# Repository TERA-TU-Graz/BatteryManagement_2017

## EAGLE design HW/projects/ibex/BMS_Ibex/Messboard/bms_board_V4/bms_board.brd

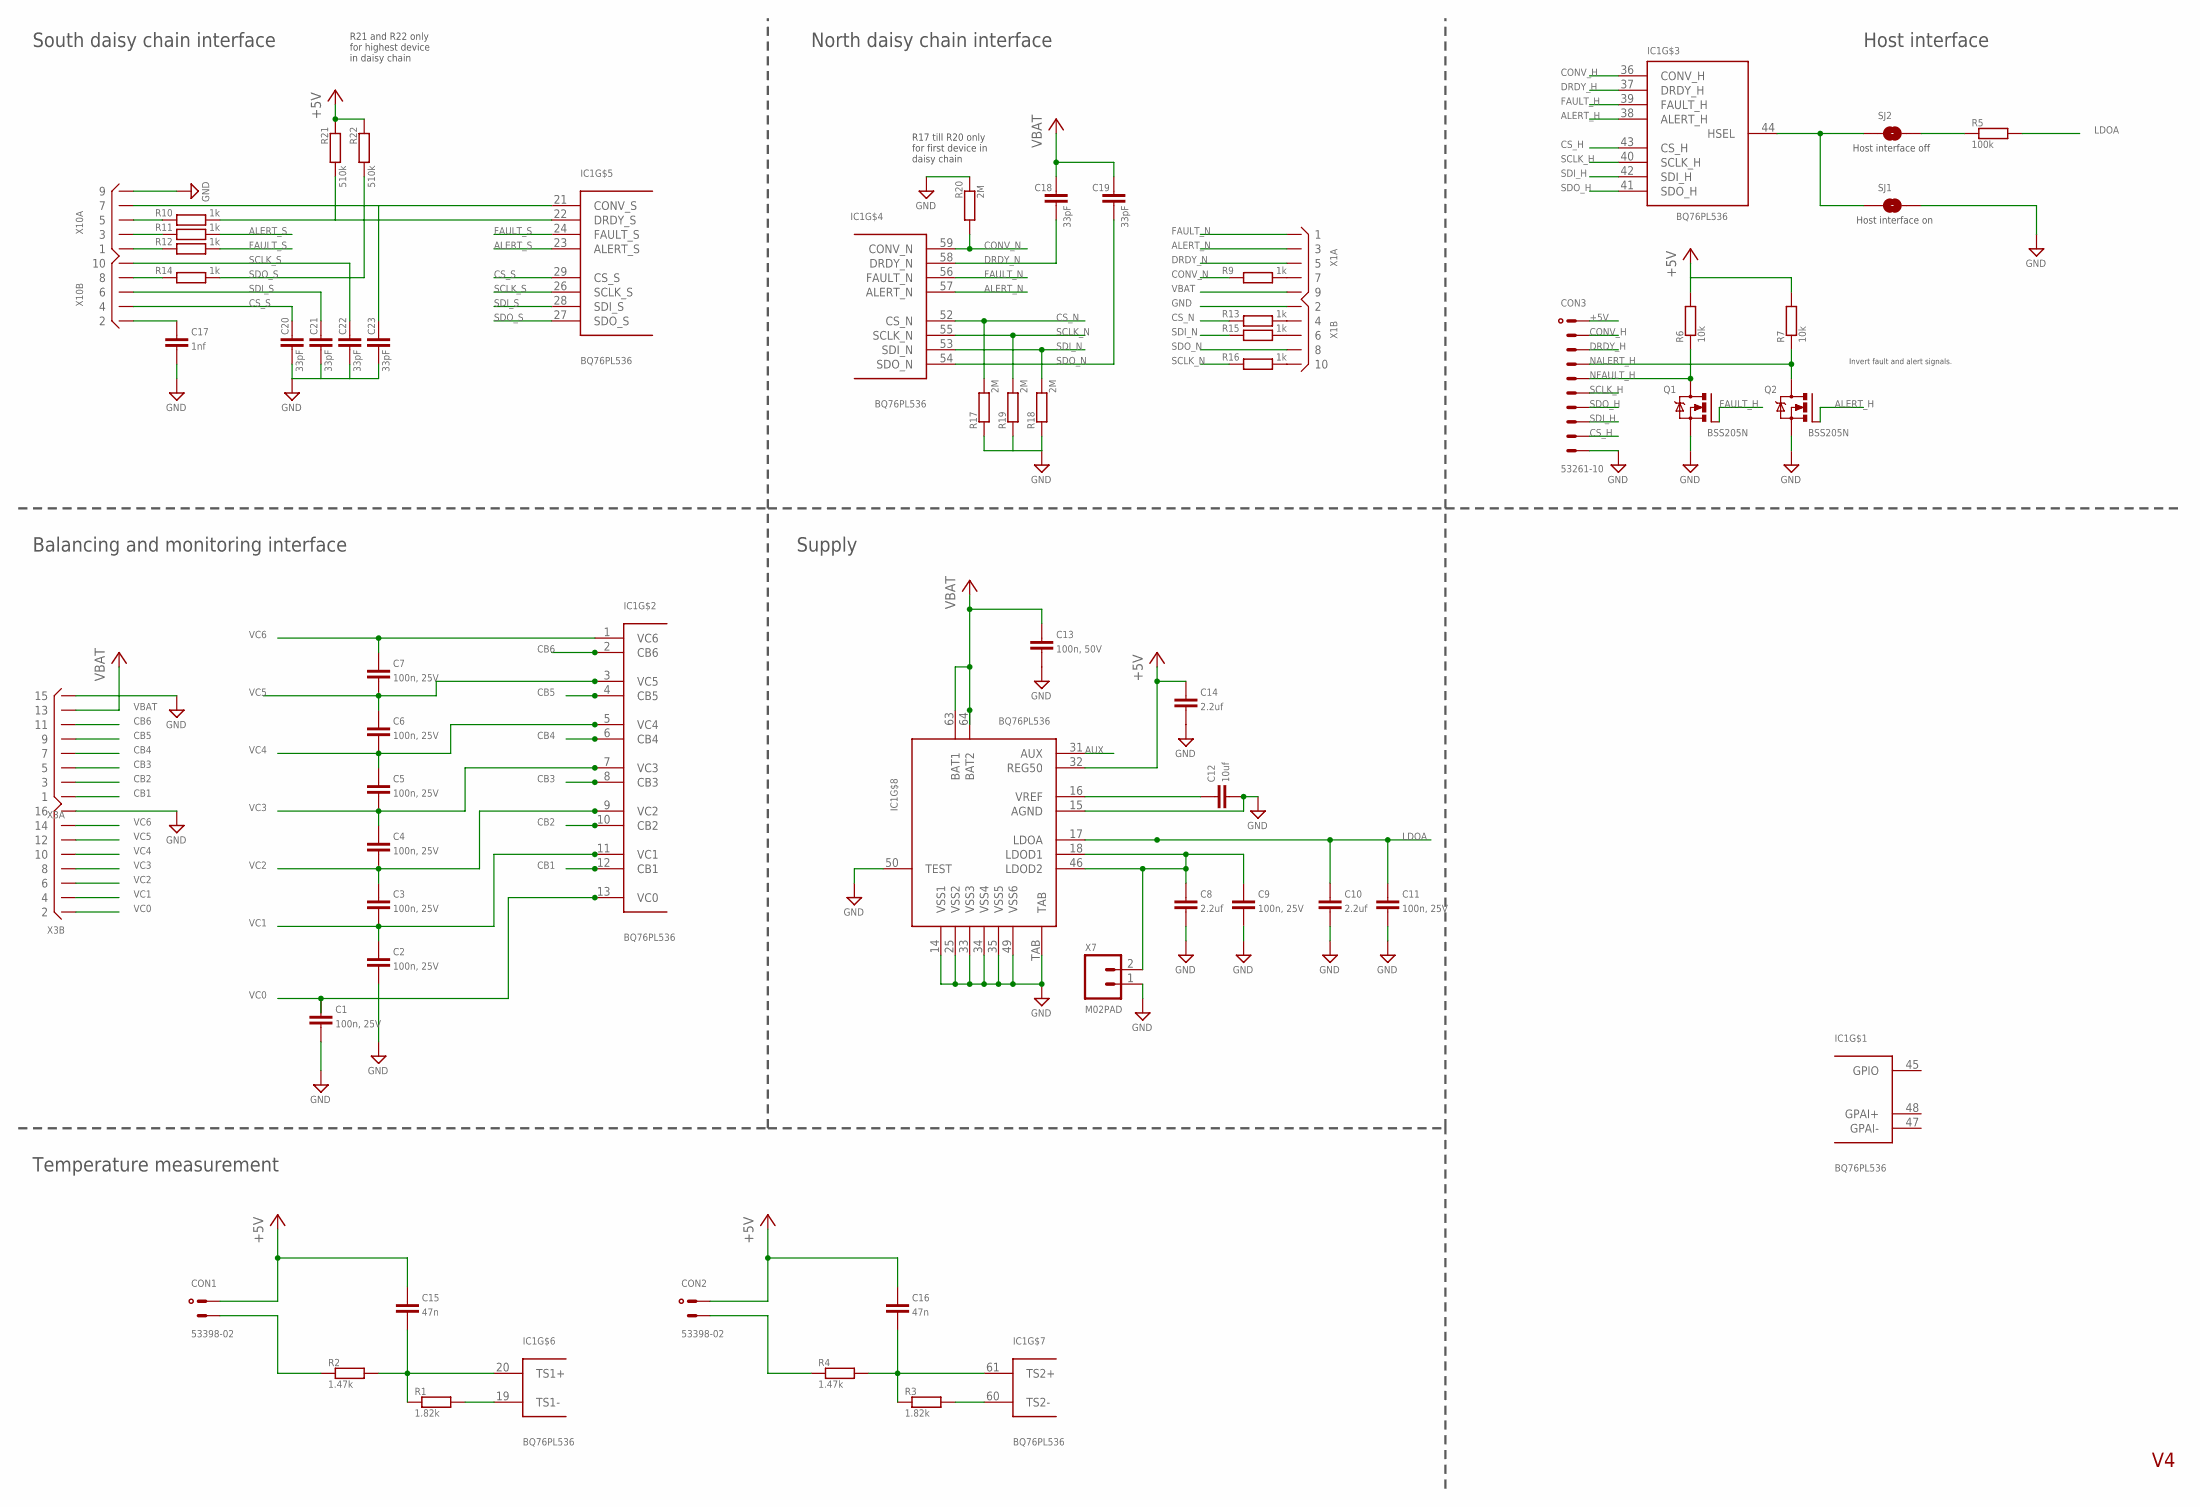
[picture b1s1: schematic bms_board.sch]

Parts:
C1, C2, C3, C4, C5, C6, C7: 100n, 25V; C0603
C8, C10, C14: 2.2uf; C0805
C9, C11: 100n, 25V; C0805
C12: 10uf; C0805
C13: 100n, 50V; C0805
C15, C16: 47n; C0805
C17: 1nf; C0805
C18, C19, C20, C21, C22, C23: 33pF; C0603
CON1, CON2: 53398-02
CON3: 53261-10
IC1: BQ76PL536; LQFP-64
Q1, Q2: BSS205N; SOT23
R1, R3: 1.82k; R0805
R2, R4: 1.47k; R0805
R5: 100k; R0805
R6, R7: 10k; R0805
R9, R10, R11, R12, R13, R14, R15, R16: 1k; R0603
R17, R18, R19, R20: 2M; R0603
R21, R22: 510k; R0603
SJ1, SJ2: SOLDERJUMPERNO; SJ_2S-NO
X1, X10: X05X2IDC-H; X10R-IDC-H
X3: X08X2DR; X16R-DIL
X7: M02PAD; 1X02

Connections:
+5V: C14.2, C15.2, C16.2, CON1.1, CON2.1, CON3.1, IC1.32 (REG50), R6.2, R7.2, R21.2, R22.2
ALERT_H: IC1.38 (ALERT_H), Q2.1 (G)
ALERT_N: IC1.57 (ALERT_N), X1.3
ALERT_S: IC1.23 (ALERT_S), R11.2
AUX: IC1.31 (AUX)
CB1: IC1.12 (CB1), X3.1
CB2: IC1.10 (CB2), X3.3
CB3: IC1.8 (CB3), X3.5
CB4: IC1.6 (CB4), X3.7
CB5: IC1.4 (CB5), X3.9
CB6: IC1.2 (CB6), X3.11
CONV_H: CON3.2, IC1.36 (CONV_H)
CONV_N: IC1.59 (CONV_N), R9.1, R20.2
CONV_S: C23.1, IC1.21 (CONV_S), X10.7
CS_H: CON3.9, IC1.43 (CS_H)
CS_N: IC1.52 (CS_N), R13.1, R17.2
CS_S: C20.1, IC1.29 (CS_S), X10.4
DRDY_H: CON3.3, IC1.37 (DRDY_H)
DRDY_N: C18.2, IC1.58 (DRDY_N), X1.5
DRDY_S: IC1.22 (DRDY_S), R10.2, R21.1
FAULT_H: IC1.39 (FAULT_H), Q1.1 (G)
FAULT_N: IC1.56 (FAULT_N), X1.1
FAULT_S: IC1.24 (FAULT_S), R12.2
GND: C1.1, C2.1, C8.1, C9.1, C10.1, C11.1, C12.1, C13.1, C14.1, C17.1, C20.2, C21.2, C22.2, C23.2, CON3.10, IC1.14 (VSS1), IC1.15 (AGND), IC1.25 (VSS2), IC1.33 (VSS3), IC1.34 (VSS4), IC1.35 (VSS5), IC1.49 (VSS6), IC1.50 (TEST), IC1.TAB, Q1.2 (S), Q2.2 (S), R17.1, R18.1, R19.1, R20.1, SJ1.2, X1.2, X3.15, X3.16, X7.1, X10.9
LDOA: C10.2, C11.2, IC1.17 (LDOA), R5.2
unnamed: IC1.44 (HSEL), SJ1.1, SJ2.1
unnamed: C8.2, C9.2, IC1.18 (LDOD1), IC1.46 (LDOD2), X7.2
unnamed: C12.2, IC1.16 (VREF)
unnamed: IC1.19 (TS1-), R1.2
unnamed: CON1.2, R2.1
unnamed: C15.1, IC1.20 (TS1+), R1.1, R2.2
unnamed: IC1.60 (TS2-), R3.2
unnamed: C16.1, IC1.61 (TS2+), R3.1, R4.2
unnamed: CON2.2, R4.1
unnamed: R5.1, SJ2.2
unnamed: R9.2, X1.7
unnamed: R13.2, X1.4
unnamed: R15.2, X1.6
unnamed: R16.2, X1.10
unnamed: R14.1, X10.8
unnamed: R12.1, X10.1
unnamed: R11.1, X10.3
unnamed: R10.1, X10.5
unnamed: C17.2, X10.2
NALERT_H: CON3.4, Q2.3 (D), R7.1
NFAULT_H: CON3.5, Q1.3 (D), R6.1
SCLK_H: CON3.6, IC1.40 (SCLK_H)
SCLK_N: IC1.55 (SCLK_N), R16.1, R19.2
SCLK_S: C22.1, IC1.26 (SCLK_S), X10.10
SDI_H: CON3.8, IC1.42 (SDI_H)
SDI_N: IC1.53 (SDI_N), R15.1, R18.2
SDI_S: C21.1, IC1.28 (SDI_S), X10.6
SDO_H: CON3.7, IC1.41 (SDO_H)
SDO_N: C19.2, IC1.54 (SDO_N), X1.8
SDO_S: IC1.27 (SDO_S), R14.2, R22.1
VBAT: C13.2, C18.1, C19.1, IC1.63 (BAT1), IC1.64 (BAT2), X1.9, X3.13
VC0: C1.2, IC1.13 (VC0), X3.2
VC1: C2.2, C3.1, IC1.11 (VC1), X3.4
VC2: C3.2, C4.1, IC1.9 (VC2), X3.6
VC3: C4.2, C5.1, IC1.7 (VC3), X3.8
VC4: C5.2, C6.1, IC1.5 (VC4), X3.10
VC5: C6.2, C7.1, IC1.3 (VC5), X3.12
VC6: C7.2, IC1.1 (VC6), X3.14

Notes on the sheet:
Host interface on
Host interface off
R17 till R20 only for first device in daisy chain
R21 and R22 only for highest device in daisy chain
South daisy chain interface
North daisy chain interface
Host interface
Balancing and monitoring interface
Supply
Temperature measurement
Invert fault and alert signals.

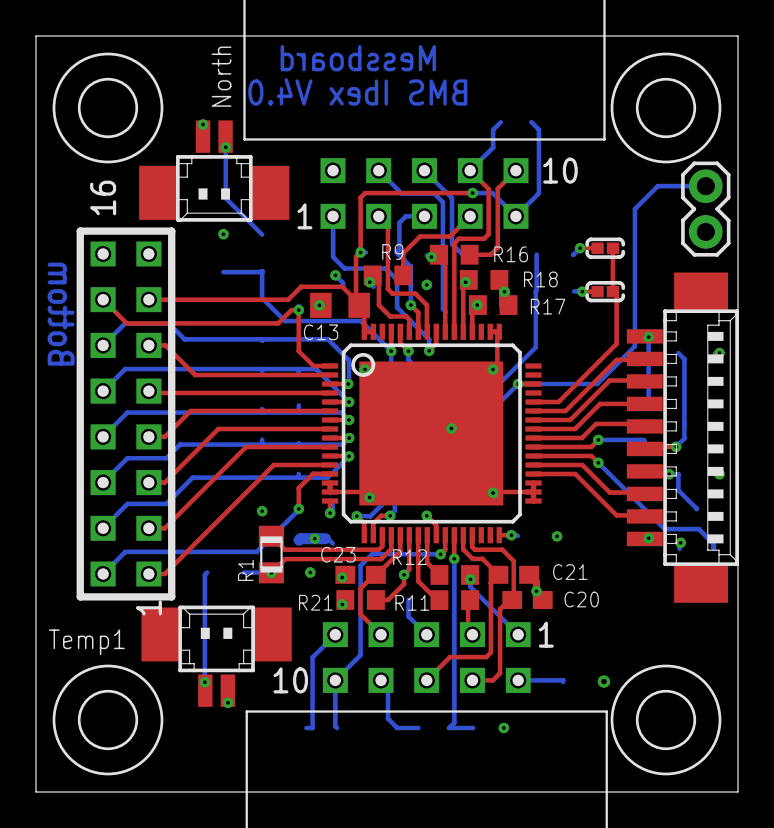
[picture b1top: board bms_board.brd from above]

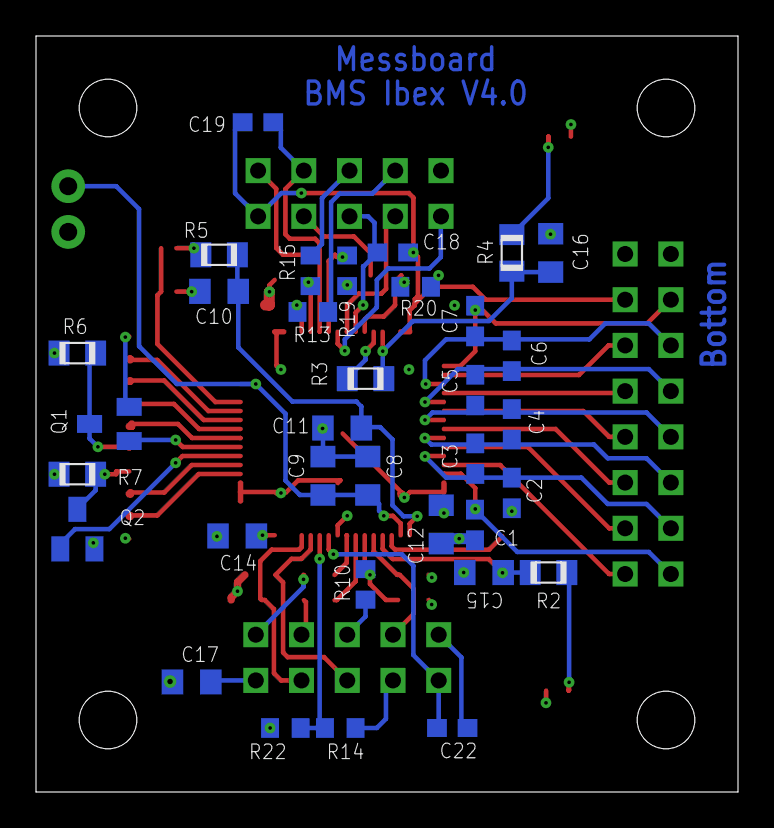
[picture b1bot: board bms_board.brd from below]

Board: 4 copper layers, 39.0 x 42.0 mm, 60 parts (34 on the bottom side), 62 nets.

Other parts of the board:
U$1, U$3, U$4, U$6: 3,2

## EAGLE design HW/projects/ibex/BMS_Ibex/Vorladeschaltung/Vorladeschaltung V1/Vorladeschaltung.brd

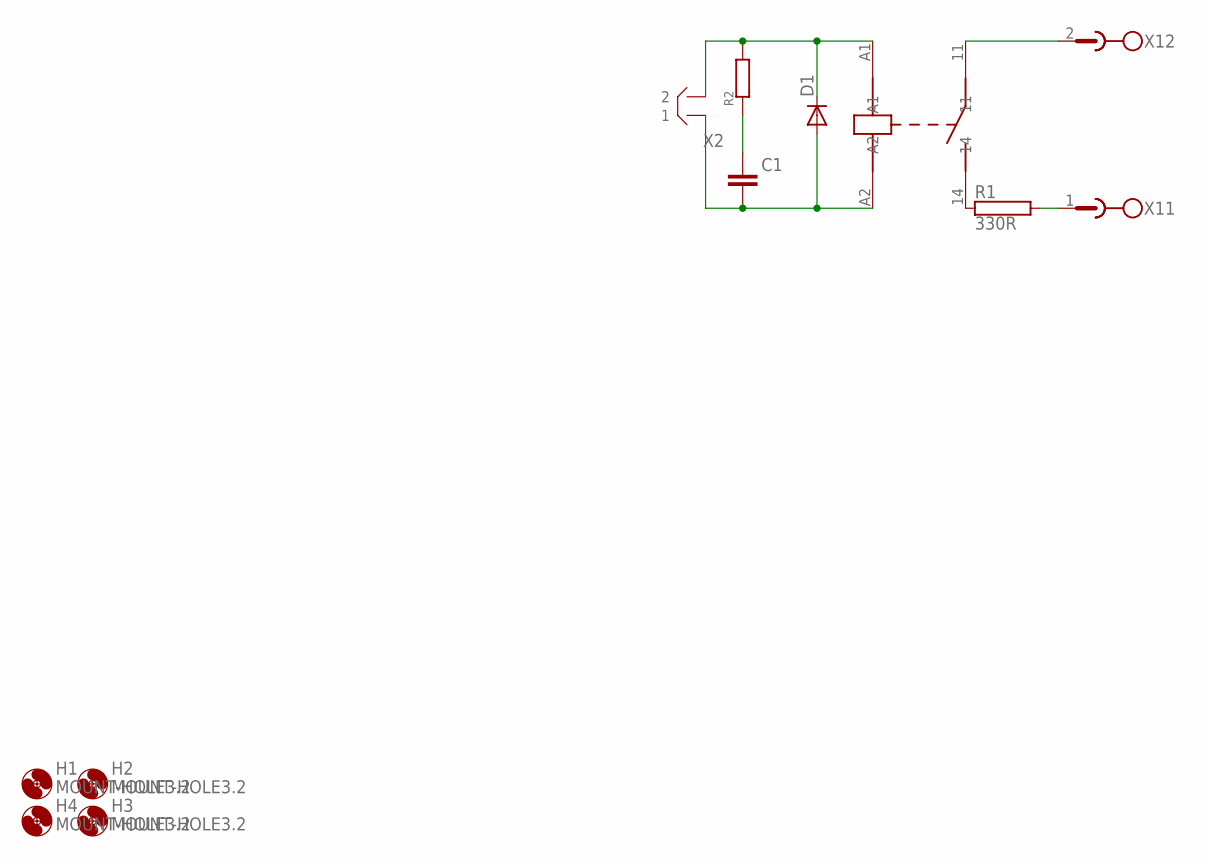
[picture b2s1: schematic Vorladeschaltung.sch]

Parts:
C1: CSTD; C0805
D1: DIODE-SOD323-W; SOD323-W
H1, H2, H3, H4: MOUNT-HOLE3.2; 3,2
K1: OJ-SH-112DMBIG; RELAIS-TE-OJ-BIG
R1: 330R; WH25
R2: R; R0805
X1: MSTBX2MSTBA2; MSTBA2
X2: B-BIG2B-XH; B2B-XH-BIG

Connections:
unnamed: K1.14, R1.1
unnamed: D1.C, K1.A1, R2.2, X2.P$2 (2)
unnamed: C1.1, D1.A, K1.A2, X2.P$1 (1)
unnamed: K1.11, X1.2
unnamed: R1.2, X1.1
unnamed: C1.2, R2.1

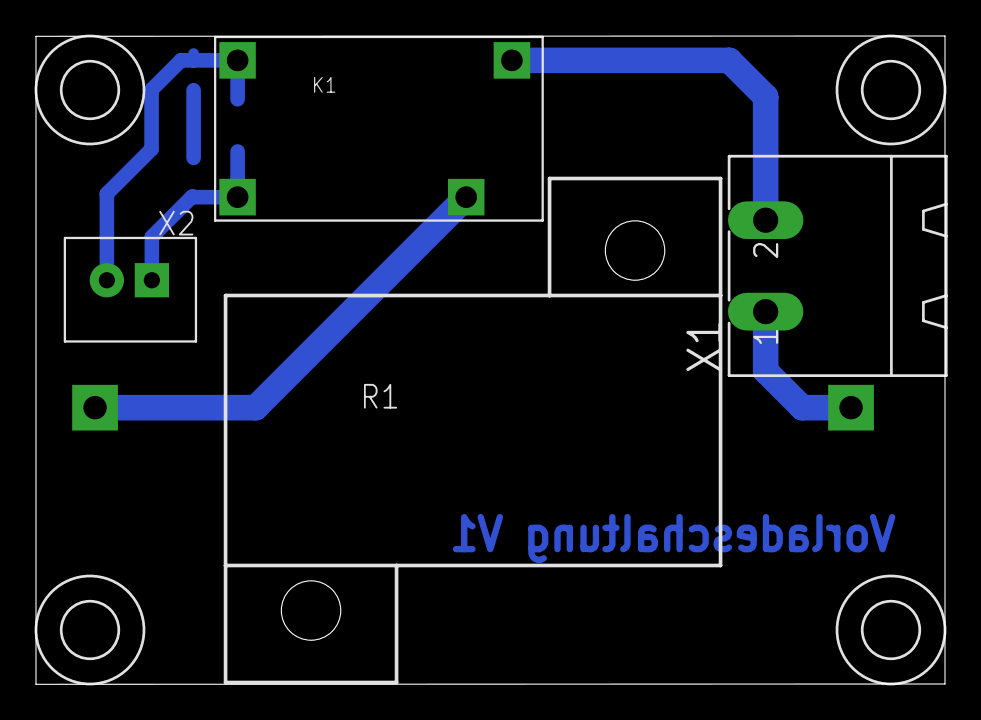
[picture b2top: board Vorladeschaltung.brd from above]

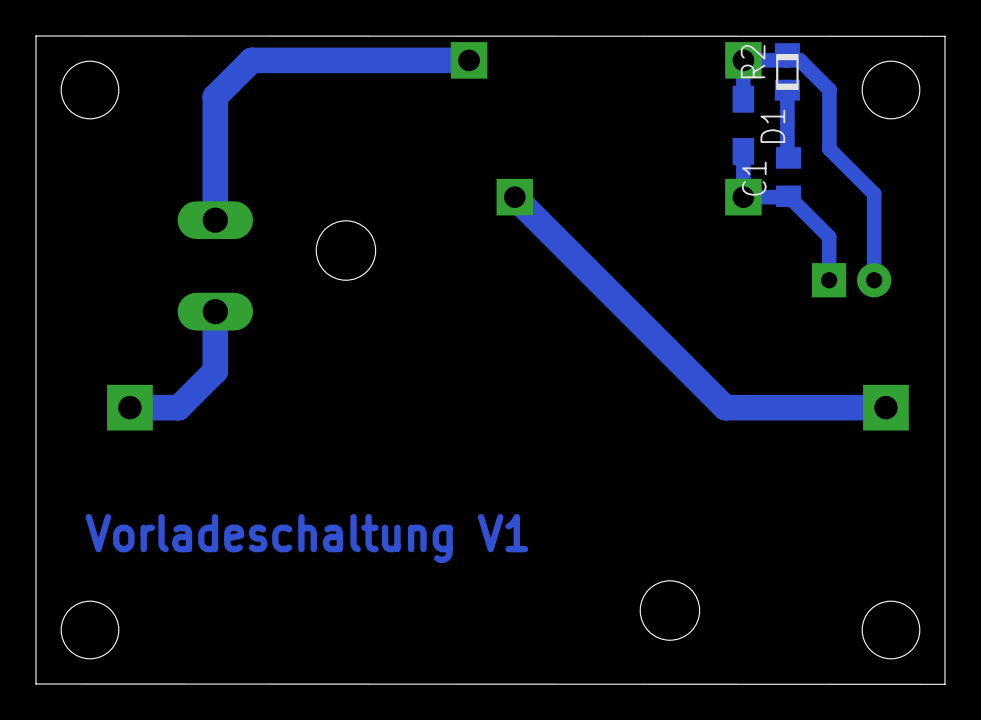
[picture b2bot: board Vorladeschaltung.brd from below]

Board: 4 copper layers, 50.5 x 36.0 mm, 11 parts (3 on the bottom side), 6 nets.

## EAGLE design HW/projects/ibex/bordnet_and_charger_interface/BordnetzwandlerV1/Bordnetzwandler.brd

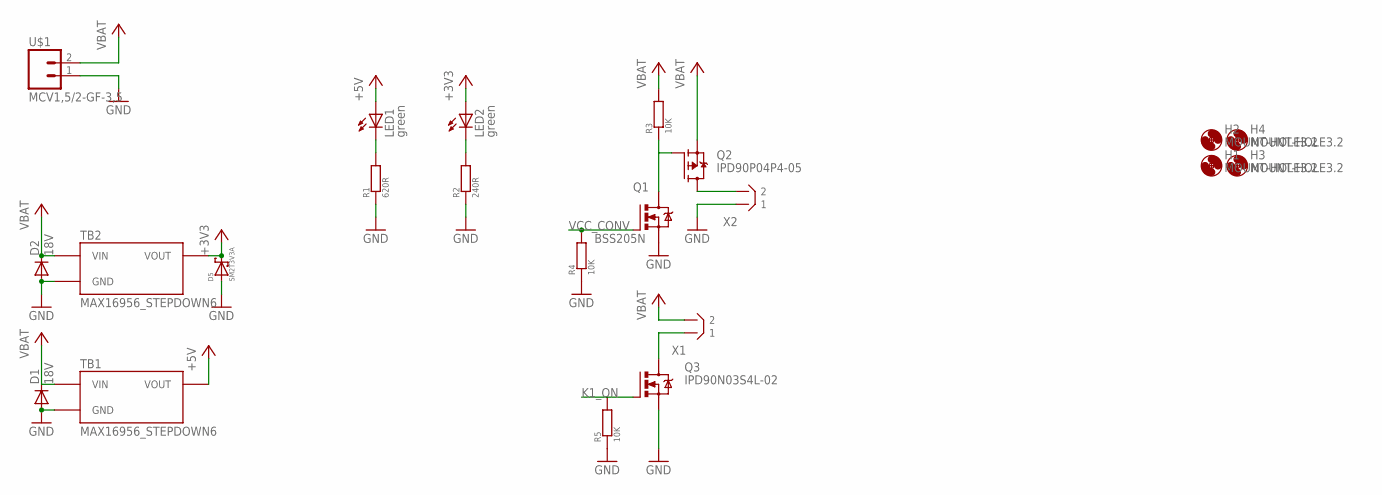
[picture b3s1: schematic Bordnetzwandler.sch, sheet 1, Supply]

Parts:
D1, D2: 18V; DO214AA
D5: SM2T3V3A
H1, H2, H3, H4: MOUNT-HOLE3.2; 3,2
LED1, LED2: green; CHIP-LED0805
Q1: BSS205N; SOT23
Q2: IPD90P04P4-05; TO252
Q3: IPD90N03S4L-02; TO252
R1: 620R; R0805
R2: 240R; R0805
R3, R4, R5: 10K; R0805
TB1, TB2: MAX16956_STEPDOWN6
U$1: MCV1,5/2-GF-3,5
X1, X2: B2B-XH

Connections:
+3V3: D5.P$2, LED2.A, TB2.VOUT; also elsewhere on the board
+5V: LED1.A, TB1.VOUT; also elsewhere on the board
GND: D1.A, D2.A, D5.P$1, D5.P$11, Q1.2 (S), Q3.3 (S), R1.1, R2.1, R4.1, R5.1, TB1.GND, TB1.GND2 (GND), TB2.GND, TB2.GND2 (GND), U$1.1, X2.P$1 (1); also elsewhere on the board
K1_ON: Q3.1 (G), R5.2; also elsewhere on the board
unnamed: LED1.C, R1.2
unnamed: LED2.C, R2.2
unnamed: Q1.3 (D), Q2.1 (G), R3.1
unnamed: Q2.2 (D), X2.P$2 (2)
unnamed: Q3.2 (D), X1.P$1 (1)
VBAT: D1.C, D2.C, Q2.3 (S), R3.2, TB1.VIN, TB2.VIN, U$1.2, X1.P$2 (2); also elsewhere on the board
VCC_CONV: Q1.1 (G), R4.2; also elsewhere on the board

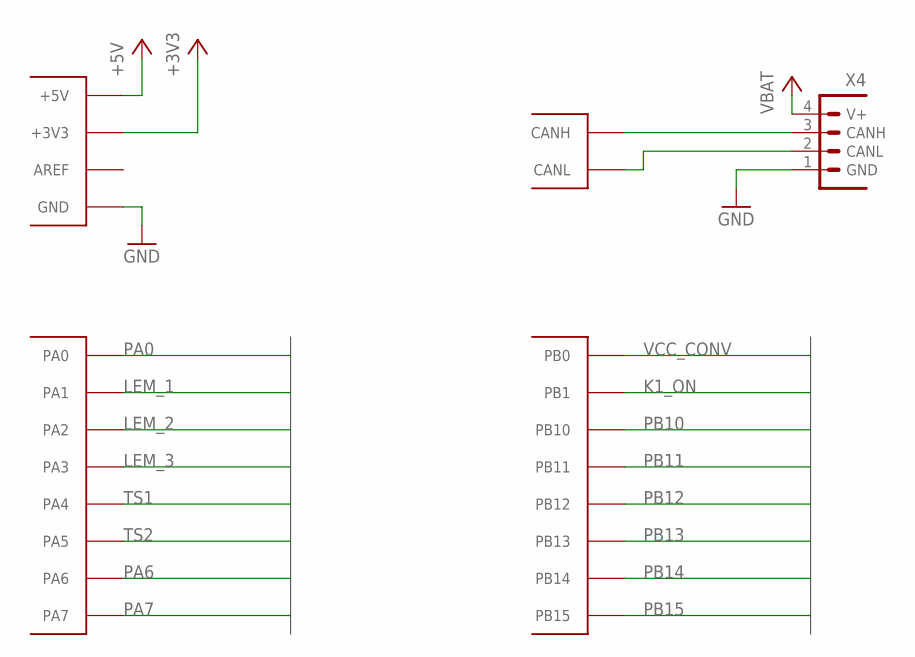
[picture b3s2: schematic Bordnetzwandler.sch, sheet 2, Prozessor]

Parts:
CANIO_1: STM32F103XX_CAN-IO-EXPANDER; STM32F103XX_CANIO-EXPANDER
X4: CIOC_4-1-FV-A_CAN-BELEGUNG; CIOC_4-1-FV

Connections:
+3V3: CANIO_1.VCC (+3V3); also elsewhere on the board
+5V: CANIO_1.+5V; also elsewhere on the board
CAN1_H: CANIO_1.CANH, X4.3 (CANH)
CAN1_L: CANIO_1.CANL, X4.2 (CANL)
GND: CANIO_1.GND1 (GND), X4.1 (GND); also elsewhere on the board
K1_ON: CANIO_1.PB1; also elsewhere on the board
LEM_1: CANIO_1.PA1; also elsewhere on the board
LEM_2: CANIO_1.PA2; also elsewhere on the board
LEM_3: CANIO_1.PA3; also elsewhere on the board
PA0: CANIO_1.PA0
PA6: CANIO_1.PA6
PA7: CANIO_1.PA7
PB10: CANIO_1.PB10
PB11: CANIO_1.PB11
PB12: CANIO_1.PB12
PB13: CANIO_1.PB13
PB14: CANIO_1.PB14
PB15: CANIO_1.PB15
TS1: CANIO_1.PA4; also elsewhere on the board
TS2: CANIO_1.PA5; also elsewhere on the board
VBAT: X4.4 (V+); also elsewhere on the board
VCC_CONV: CANIO_1.PB0; also elsewhere on the board

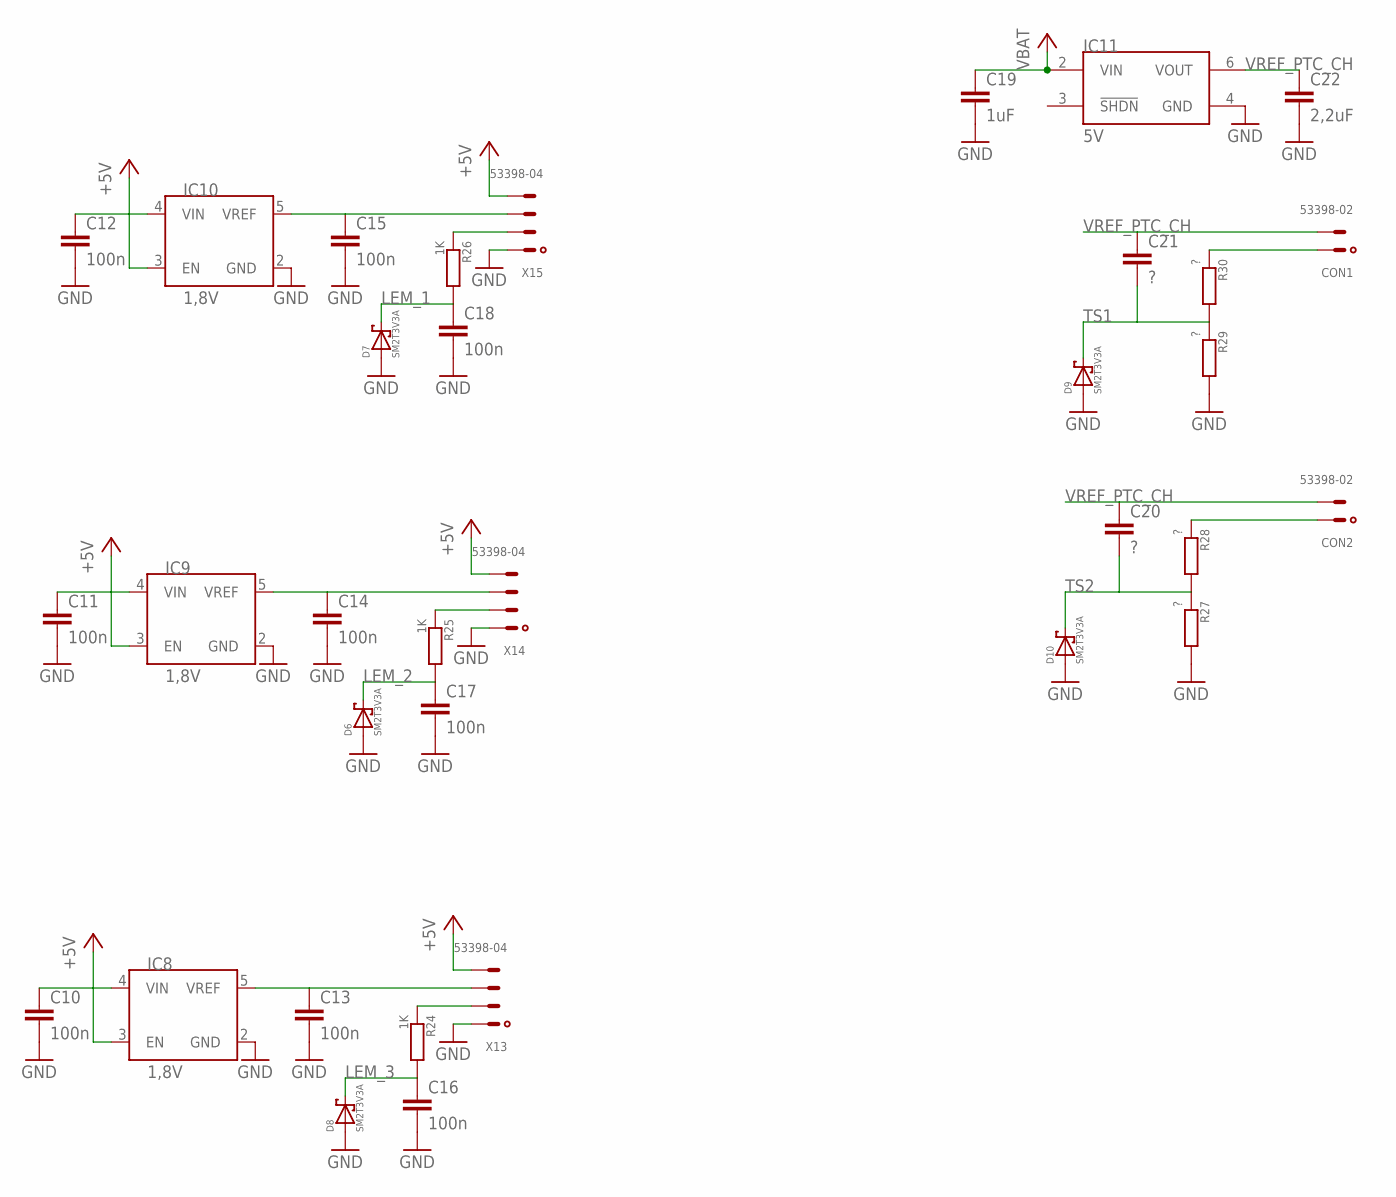
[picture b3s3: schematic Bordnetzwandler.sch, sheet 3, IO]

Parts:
C10, C11, C12, C13, C14, C15, C16, C17, C18: 100n; C0805
C19: 1uF; C0805
C20, C21: ?; C0805
C22: 2,2uF; C0805
CON1, CON2: 53398-02
D6, D7, D8, D9, D10: SM2T3V3A
IC8, IC9, IC10: 1,8V; SOT23-5L
IC11: 5V; SO08
R24, R25, R26: 1K; R0805
R27, R28, R29, R30: ?; R0805
X13, X14, X15: 53398-04

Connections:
+5V: C10.1, C11.1, C12.1, IC8.3 (EN), IC8.4 (VIN), IC9.3 (EN), IC9.4 (VIN), IC10.3 (EN), IC10.4 (VIN), X13.4, X14.4, X15.4; also elsewhere on the board
GND: C10.2, C11.2, C12.2, C13.2, C14.2, C15.2, C16.2, C17.2, C18.2, C19.2, C22.2, D6.P$1, D6.P$11, D7.P$1, D7.P$11, D8.P$1, D8.P$11, D9.P$1, D9.P$11, D10.P$1, D10.P$11, IC8.2 (GND), IC9.2 (GND), IC10.2 (GND), IC11.4 (GND), R27.2, R29.2, X13.1, X14.1, X15.1; also elsewhere on the board
LEM_1: C18.1, D7.P$2, R26.2; also elsewhere on the board
LEM_2: C17.1, D6.P$2, R25.2; also elsewhere on the board
LEM_3: C16.1, D8.P$2, R24.2; also elsewhere on the board
unnamed: C13.1, IC8.5 (VREF), X13.3
unnamed: R26.1, X15.2
unnamed: C14.1, IC9.5 (VREF), X14.3
unnamed: CON1.1, R30.1
unnamed: R25.1, X14.2
unnamed: C15.1, IC10.5 (VREF), X15.3
unnamed: R24.1, X13.2
unnamed: CON2.1, R28.1
TS1: C21.2, D9.P$2, R29.1, R30.2; also elsewhere on the board
TS2: C20.2, D10.P$2, R27.1, R28.2; also elsewhere on the board
VBAT: C19.1, IC11.2 (VIN); also elsewhere on the board
VREF_PTC_CH: C20.1, C21.1, C22.1, CON1.2, CON2.2, IC11.6 (VOUT)

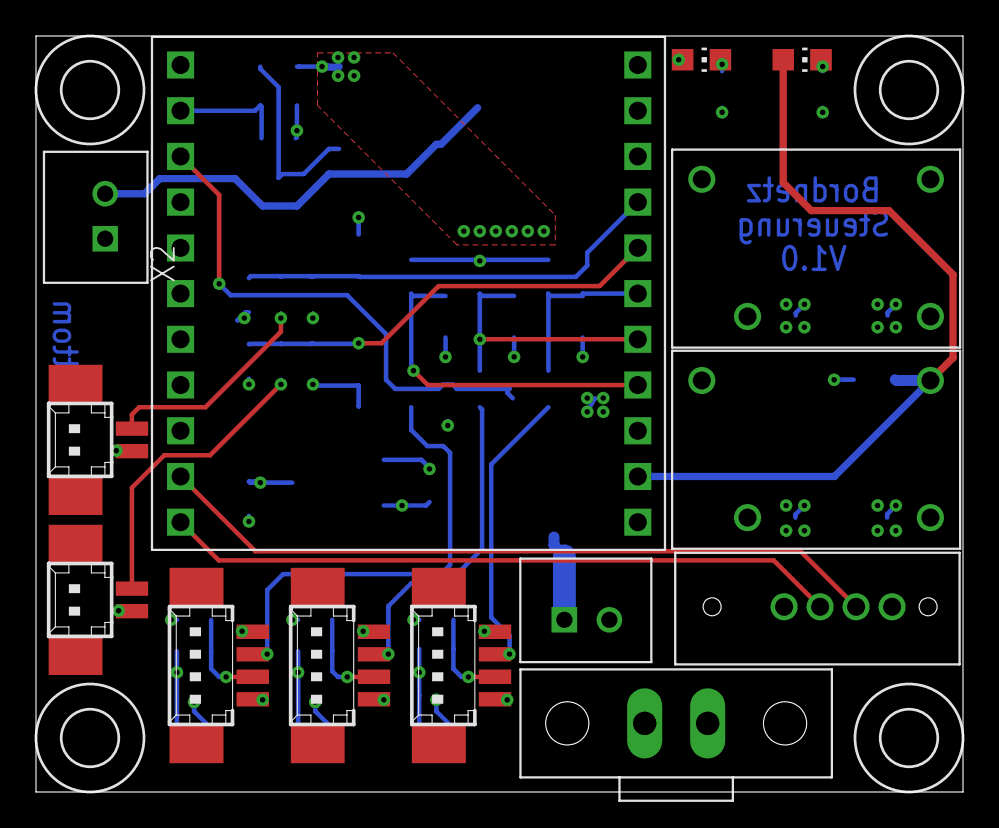
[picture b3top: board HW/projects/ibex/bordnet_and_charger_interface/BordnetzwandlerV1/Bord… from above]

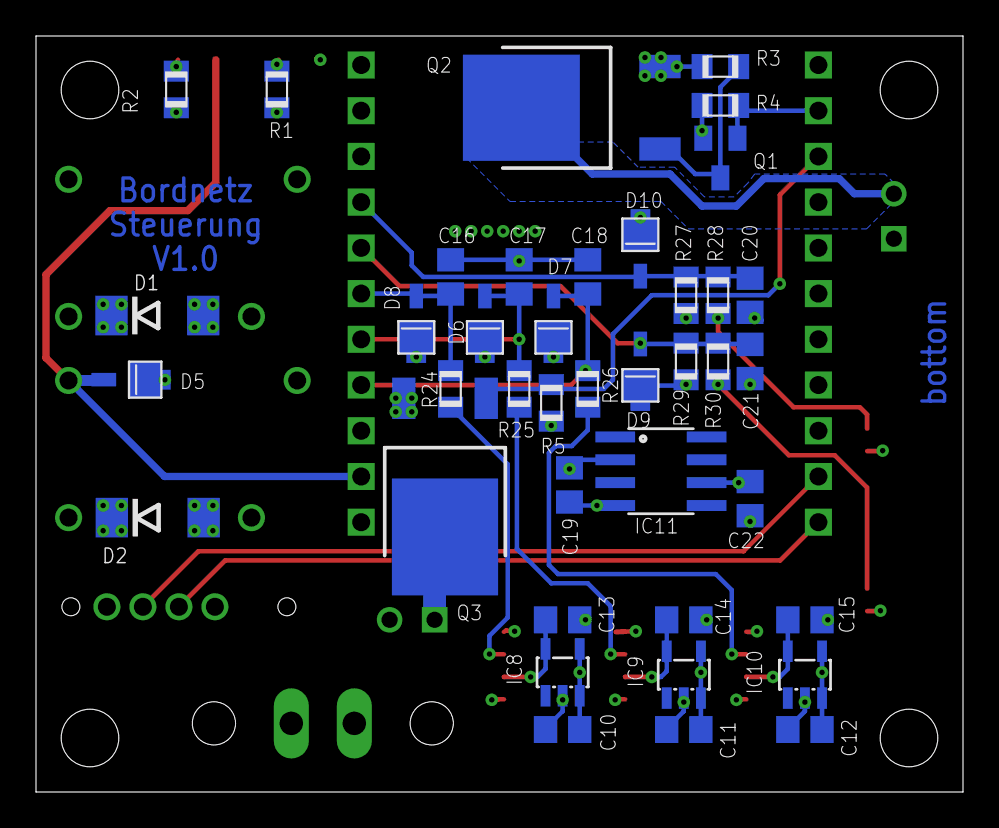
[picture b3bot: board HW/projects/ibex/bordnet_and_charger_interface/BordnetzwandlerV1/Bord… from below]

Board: 4 copper layers, 51.5 x 42.0 mm, 58 parts (40 on the bottom side), 27 nets.

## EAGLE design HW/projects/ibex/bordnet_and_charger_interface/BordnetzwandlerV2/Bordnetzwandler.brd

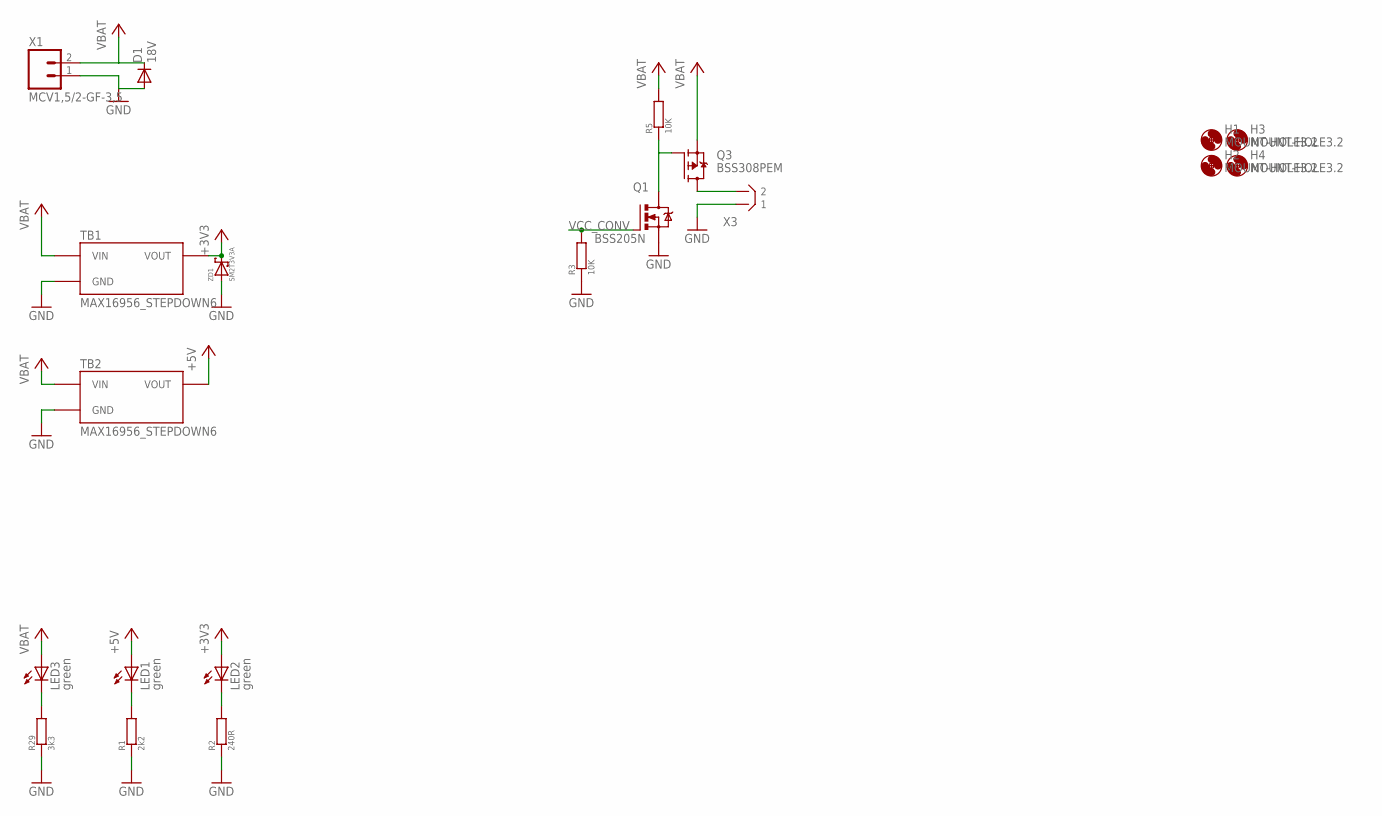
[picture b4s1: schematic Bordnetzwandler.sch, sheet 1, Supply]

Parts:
D1: 18V; DO214AA
H1, H2, H3, H4: MOUNT-HOLE3.2; 3,2
LED1, LED2, LED3: green; CHIP-LED0805
Q1: BSS205N; SOT23
Q3: BSS308PEM; INF-PG-SOT23_M_1PRIMARY
R1: 2k2; R0805
R2: 240R; R0805
R3, R5: 10K; R0805
R29: 3k3; R0805
TB1, TB2: MAX16956_STEPDOWN6
X1: MCV1,5/2-GF-3,5
X3: B2B-XH
ZD1: SM2T3V3A

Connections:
+3V3: LED2.A, TB1.VOUT, ZD1.P$2; also elsewhere on the board
+5V: LED1.A, TB2.VOUT; also elsewhere on the board
GND: D1.A, Q1.2 (S), R1.1, R2.1, R3.1, R29.1, TB1.GND, TB1.GND2 (GND), TB2.GND, TB2.GND2 (GND), X1.1, X3.P$1 (1), ZD1.P$1, ZD1.P$11; also elsewhere on the board
unnamed: LED1.C, R1.2
unnamed: LED2.C, R2.2
unnamed: Q1.3 (D), Q3.1 (G), R5.1
unnamed: LED3.C, R29.2
unnamed: Q3.3 (D), X3.P$2 (2)
VBAT: D1.C, LED3.A, Q3.2 (S), R5.2, TB1.VIN, TB2.VIN, X1.2; also elsewhere on the board
VCC_CONV: Q1.1 (G), R3.2; also elsewhere on the board

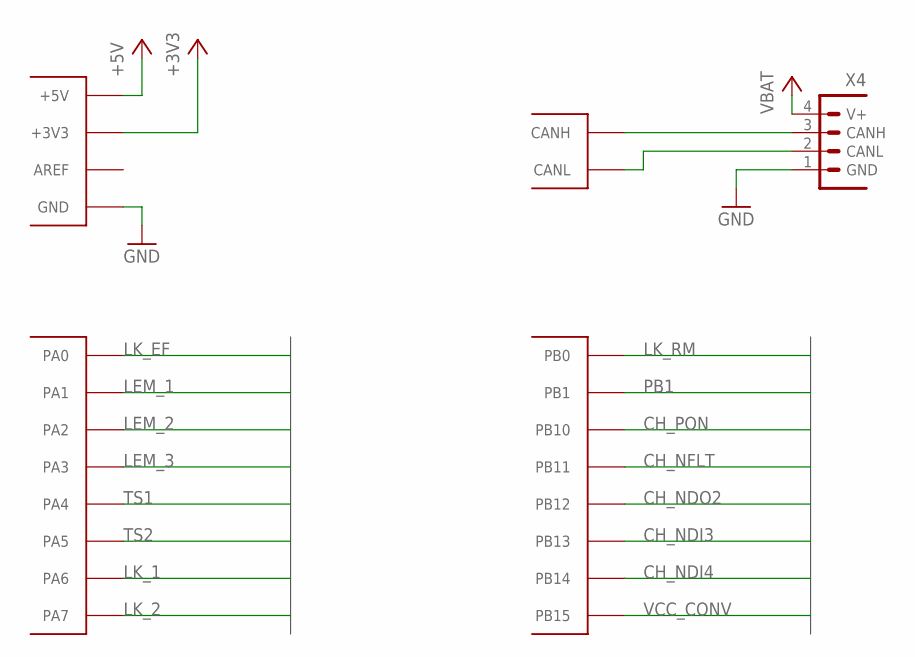
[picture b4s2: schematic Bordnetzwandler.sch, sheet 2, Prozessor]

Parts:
CANIO_1: STM32F103XX_CAN-IO-EXPANDER; STM32F103XX_CANIO-EXPANDER
X4: CIOC_4-1-FV-A_CAN-BELEGUNG; CIOC_4-1-FV

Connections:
+3V3: CANIO_1.VCC (+3V3); also elsewhere on the board
+5V: CANIO_1.+5V; also elsewhere on the board
CAN1_H: CANIO_1.CANH, X4.3 (CANH)
CAN1_L: CANIO_1.CANL, X4.2 (CANL)
CH_NDI3: CANIO_1.PB13; also elsewhere on the board
CH_NDI4: CANIO_1.PB14; also elsewhere on the board
CH_NDO2: CANIO_1.PB12; also elsewhere on the board
CH_NFLT: CANIO_1.PB11; also elsewhere on the board
CH_PON: CANIO_1.PB10; also elsewhere on the board
GND: CANIO_1.GND1 (GND), X4.1 (GND); also elsewhere on the board
LEM_1: CANIO_1.PA1; also elsewhere on the board
LEM_2: CANIO_1.PA2; also elsewhere on the board
LEM_3: CANIO_1.PA3; also elsewhere on the board
LK_1: CANIO_1.PA6; also elsewhere on the board
LK_2: CANIO_1.PA7; also elsewhere on the board
LK_EF: CANIO_1.PA0; also elsewhere on the board
LK_RM: CANIO_1.PB0; also elsewhere on the board
PB1: CANIO_1.PB1
TS1: CANIO_1.PA4; also elsewhere on the board
TS2: CANIO_1.PA5; also elsewhere on the board
VBAT: X4.4 (V+); also elsewhere on the board
VCC_CONV: CANIO_1.PB15; also elsewhere on the board

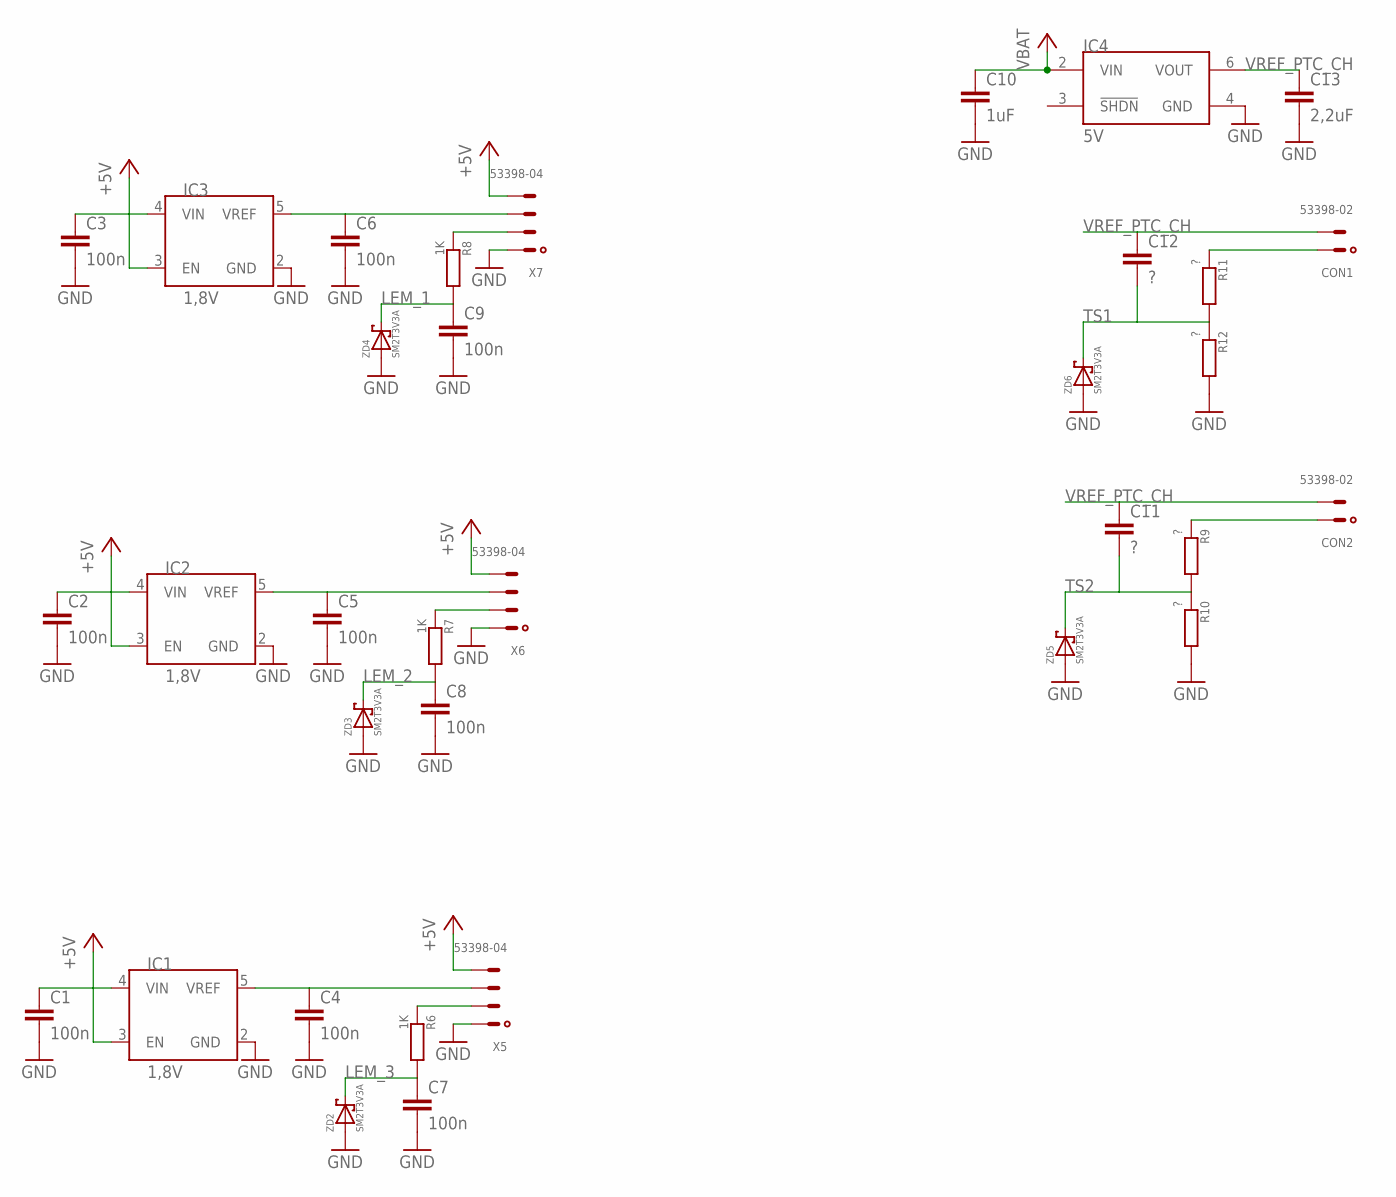
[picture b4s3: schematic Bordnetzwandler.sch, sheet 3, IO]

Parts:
C1, C2, C3, C4, C5, C6, C7, C8, C9: 100n; C0805
C10: 1uF; C0805
C11, C12: ?; C0805
C13: 2,2uF; C0805
CON1, CON2: 53398-02
IC1, IC2, IC3: 1,8V; SOT23-5L
IC4: 5V; SO08
R6, R7, R8: 1K; R0805
R9, R10, R11, R12: ?; R0805
X5, X6, X7: 53398-04
ZD2, ZD3, ZD4, ZD5, ZD6: SM2T3V3A

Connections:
+5V: C1.1, C2.1, C3.1, IC1.3 (EN), IC1.4 (VIN), IC2.3 (EN), IC2.4 (VIN), IC3.3 (EN), IC3.4 (VIN), X5.4, X6.4, X7.4; also elsewhere on the board
GND: C1.2, C2.2, C3.2, C4.2, C5.2, C6.2, C7.2, C8.2, C9.2, C10.2, C13.2, IC1.2 (GND), IC2.2 (GND), IC3.2 (GND), IC4.4 (GND), R10.2, R12.2, X5.1, X6.1, X7.1, ZD2.P$1, ZD2.P$11, ZD3.P$1, ZD3.P$11, ZD4.P$1, ZD4.P$11, ZD5.P$1, ZD5.P$11, ZD6.P$1, ZD6.P$11; also elsewhere on the board
LEM_1: C9.1, R8.2, ZD4.P$2; also elsewhere on the board
LEM_2: C8.1, R7.2, ZD3.P$2; also elsewhere on the board
LEM_3: C7.1, R6.2, ZD2.P$2; also elsewhere on the board
unnamed: C4.1, IC1.5 (VREF), X5.3
unnamed: R8.1, X7.2
unnamed: C5.1, IC2.5 (VREF), X6.3
unnamed: CON1.1, R11.1
unnamed: R7.1, X6.2
unnamed: C6.1, IC3.5 (VREF), X7.3
unnamed: R6.1, X5.2
unnamed: CON2.1, R9.1
TS1: C12.2, R11.2, R12.1, ZD6.P$2; also elsewhere on the board
TS2: C11.2, R9.2, R10.1, ZD5.P$2; also elsewhere on the board
VBAT: C10.1, IC4.2 (VIN); also elsewhere on the board
VREF_PTC_CH: C11.1, C12.1, C13.1, CON1.2, CON2.2, IC4.6 (VOUT)

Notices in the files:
parts and their libraries:
SparkFun: Licensing: CC v3.0 Share-Alike You are welcome to use this library for commercial purposes.
